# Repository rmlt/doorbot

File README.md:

# doorbot
Software for our DoorBot

The DoorBot is a device connected to our doorphone that opens the office doors as required.

This software runs on a Raspberry Pi connected to a circuit board that allows it to:
* get input from the doorphone LED and the doorbell button
* simulate pressing a button on the doorphone
* move a servo attached to the door handle
* play sounds

TODO:
* black, isort
* split into modules
* logging instead of printing
* add some photos

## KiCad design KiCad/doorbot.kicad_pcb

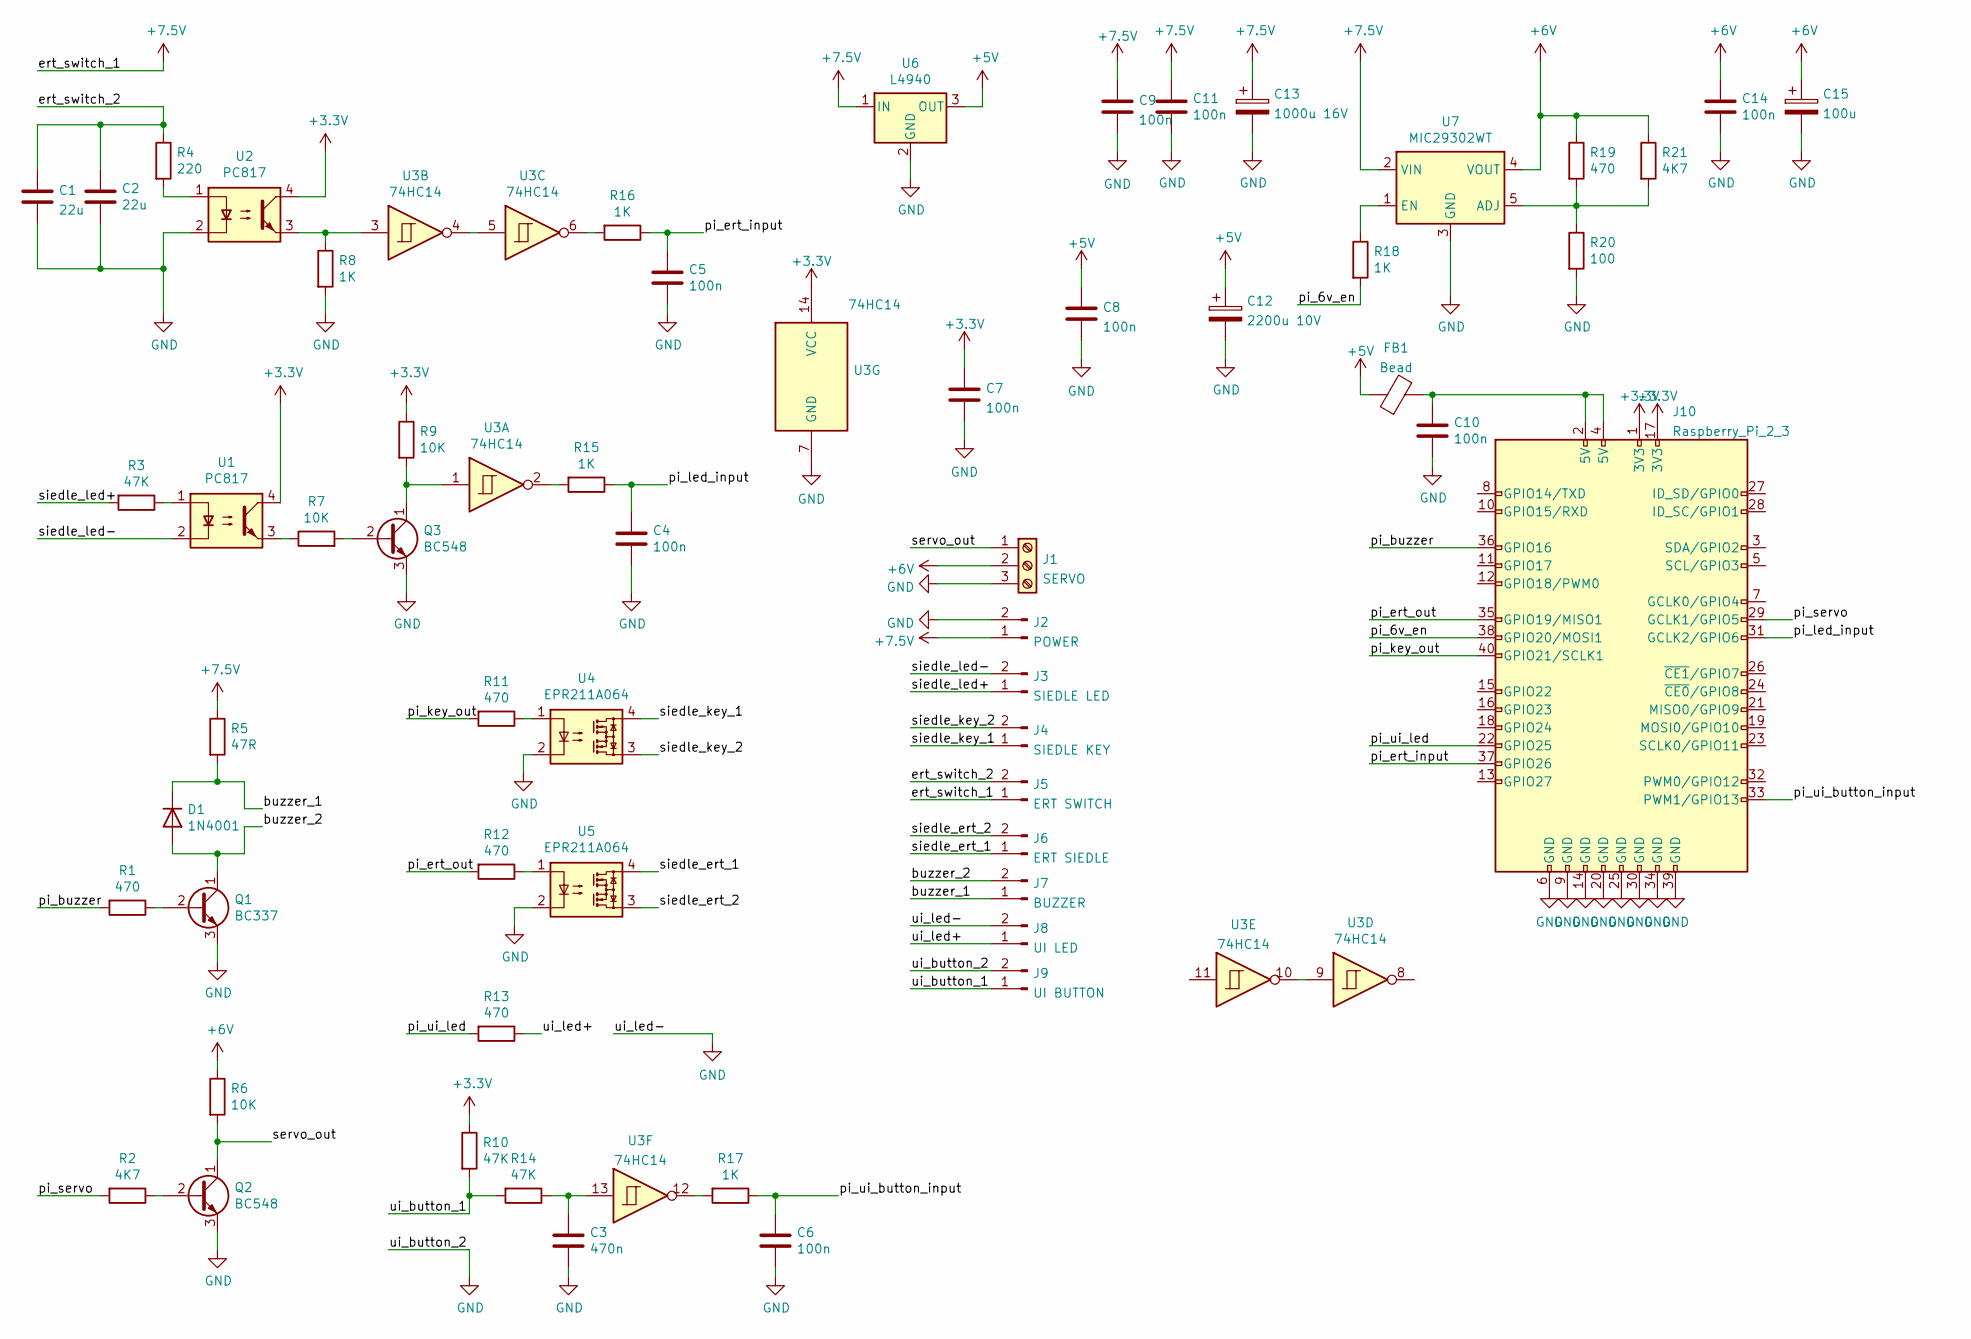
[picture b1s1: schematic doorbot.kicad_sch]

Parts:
C1, C2: 22u; C_1210_3225Metric
C3: 470n; C_Disc_D5.0mm_W2.5mm_P2.50mm
C4, C5, C6, C8, C9, C10, C11, C14: 100n; C_Disc_D5.0mm_W2.5mm_P2.50mm
C7: 100n; C_Disc_D7.5mm_W5.0mm_P7.50mm
C12: 2200u 10V; CP_Radial_D12.5mm_P5.00mm
C13: 1000u 16V; CP_Radial_D12.5mm_P5.00mm
C15: 100u; CP_Radial_D10.0mm_P2.50mm
D1: 1N4001; D_DO-41_SOD81_P2.54mm_Vertical_AnodeUp
FB1: Bead; R_Axial_DIN0207_L6.3mm_D2.5mm_P10.16mm_Horizontal
J1: SERVO; TerminalBlock_bornier-3_P5.08mm
J2: POWER; PinHeader_1x02_P2.54mm_Vertical
J3: SIEDLE LED; PinHeader_1x02_P2.54mm_Vertical
J4: SIEDLE KEY; PinHeader_1x02_P2.54mm_Vertical
J5: ERT SWITCH; PinHeader_1x02_P2.54mm_Vertical
J6: ERT SIEDLE; PinHeader_1x02_P2.54mm_Vertical
J7: BUZZER; PinHeader_1x02_P2.54mm_Vertical
J8: UI LED; PinHeader_1x02_P2.54mm_Vertical
J9: UI BUTTON; PinHeader_1x02_P2.54mm_Vertical
J10: Raspberry_Pi_2_3; PinSocket_2x20_P2.54mm_Vertical
Q1: BC337; TO-92_Inline_Wide
Q2, Q3: BC548; TO-92_Inline_Wide
R1, R19: 470; R_Axial_DIN0207_L6.3mm_D2.5mm_P2.54mm_Vertical
R2, R21: 4K7; R_Axial_DIN0207_L6.3mm_D2.5mm_P2.54mm_Vertical
R3, R14: 47K; R_Axial_DIN0207_L6.3mm_D2.5mm_P5.08mm_Vertical
R4: 220; R_Axial_DIN0207_L6.3mm_D2.5mm_P2.54mm_Vertical
R5: 47R; R_Axial_DIN0207_L6.3mm_D2.5mm_P5.08mm_Vertical
R6: 10K; R_Axial_DIN0207_L6.3mm_D2.5mm_P2.54mm_Vertical
R7, R9: 10K; R_Axial_DIN0207_L6.3mm_D2.5mm_P10.16mm_Horizontal
R8: 1K; R_Axial_DIN0207_L6.3mm_D2.5mm_P10.16mm_Horizontal
R10: 47K; R_Axial_DIN0309_L9.0mm_D3.2mm_P12.70mm_Horizontal
R11, R13: 470; R_Axial_DIN0207_L6.3mm_D2.5mm_P5.08mm_Vertical
R12: 470; R_Axial_DIN0207_L6.3mm_D2.5mm_P10.16mm_Horizontal
R15: 1K; R_Axial_DIN0309_L9.0mm_D3.2mm_P12.70mm_Horizontal
R16: 1K; R_Axial_DIN0207_L6.3mm_D2.5mm_P15.24mm_Horizontal
R17: 1K; R_Axial_DIN0207_L6.3mm_D2.5mm_P2.54mm_Vertical
R18: 1K; R_Axial_DIN0207_L6.3mm_D2.5mm_P5.08mm_Vertical
R20: 100; R_Axial_DIN0207_L6.3mm_D2.5mm_P5.08mm_Vertical
U1, U2: PC817; DIP-4_W7.62mm
U3: 74HC14; DIP-14_W7.62mm
U4, U5: EPR211A064; DIP-4_W7.62mm
U6: L4940; TO-220-3_Horizontal_TabDown
U7: MIC29302WT; R_Array_SIP5

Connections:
+3V3: C7.1, J10.1 (3V3), J10.17 (3V3), R9.1, R10.1, U1.4, U2.4, U3.14 (VCC)
+5V: C8.1, C12.1, FB1.1, U6.3 (OUT)
+6V: C14.1, C15.1, J1.2, R6.1, R19.1, R21.1, U7.4 (VOUT)
+7.5V: C9.1, C11.1, C13.1, J2.1, J5.1, R5.1, U6.1 (IN), U7.2 (VIN)
/buzzer_1: D1.1 (K), J7.1, R5.2
/buzzer_2: D1.2 (A), J7.2, Q1.1 (C)
/ert_switch_2: C1.1, C2.1, J5.2, R4.1
/pi_6v_en: J10.38 (GPIO20/MOSI1), R18.2
/pi_buzzer: J10.36 (GPIO16), R1.2
/pi_ert_input: C5.1, J10.37 (GPIO26), R16.1
/pi_ert_out: J10.35 (GPIO19/MISO1), R12.2
/pi_key_out: J10.40 (GPIO21/SCLK1), R11.2
/pi_led_input: C4.1, J10.31 (GCLK2/GPIO6), R15.1
/pi_servo: J10.29 (GCLK1/GPIO5), R2.2
/pi_ui_button_input: C6.1, J10.33 (PWM1/GPIO13), R17.1
/pi_ui_led: J10.22 (GPIO25), R13.2
/servo_out: J1.1, Q2.1 (C), R6.2
/siedle_ert_1: J6.1, U5.4
/siedle_ert_2: J6.2, U5.3
/siedle_key_1: J4.1, U4.4
/siedle_key_2: J4.2, U4.3
/siedle_led+: J3.1, R3.2
/siedle_led-: J3.2, U1.2
/ui_button_1: J9.1, R10.2, R14.2
/ui_led+: J8.1, R13.1
GND: C1.2, C2.2, C3.2, C4.2, C5.2, C6.2, C7.2, C8.2, C9.2, C10.2, C11.2, C12.2, C13.2, C14.2, C15.2, J1.3, J2.2, J8.2, J9.2, J10.6 (GND), J10.9 (GND), J10.14 (GND), J10.20 (GND), J10.25 (GND), J10.30 (GND), J10.34 (GND), J10.39 (GND), Q1.3 (E), Q2.3 (E), Q3.3 (E), R8.2, R20.2, U2.2, U3.7 (GND), U4.2, U5.2, U6.2 (GND), U7.3 (GND)
unnamed: C3.1, R14.1, U3.13
unnamed: C10.1, FB1.2, J10.2 (5V), J10.4 (5V)
unnamed: Q1.2 (B), R1.1
unnamed: Q2.2 (B), R2.1
unnamed: Q3.1 (C), R9.2, U3.1
unnamed: Q3.2 (B), R7.2
unnamed: R3.1, U1.1
unnamed: R4.2, U2.1
unnamed: R7.1, U1.3
unnamed: R8.1, U2.3, U3.3
unnamed: R11.1, U4.1
unnamed: R12.1, U5.1
unnamed: R15.2, U3.2
unnamed: R16.2, U3.6
unnamed: R17.2, U3.12
unnamed: R18.1, U7.1 (EN)
unnamed: R19.2, R20.1, R21.2, U7.5 (ADJ)
unnamed: U3.4, U3.5
unnamed: U3.9, U3.10

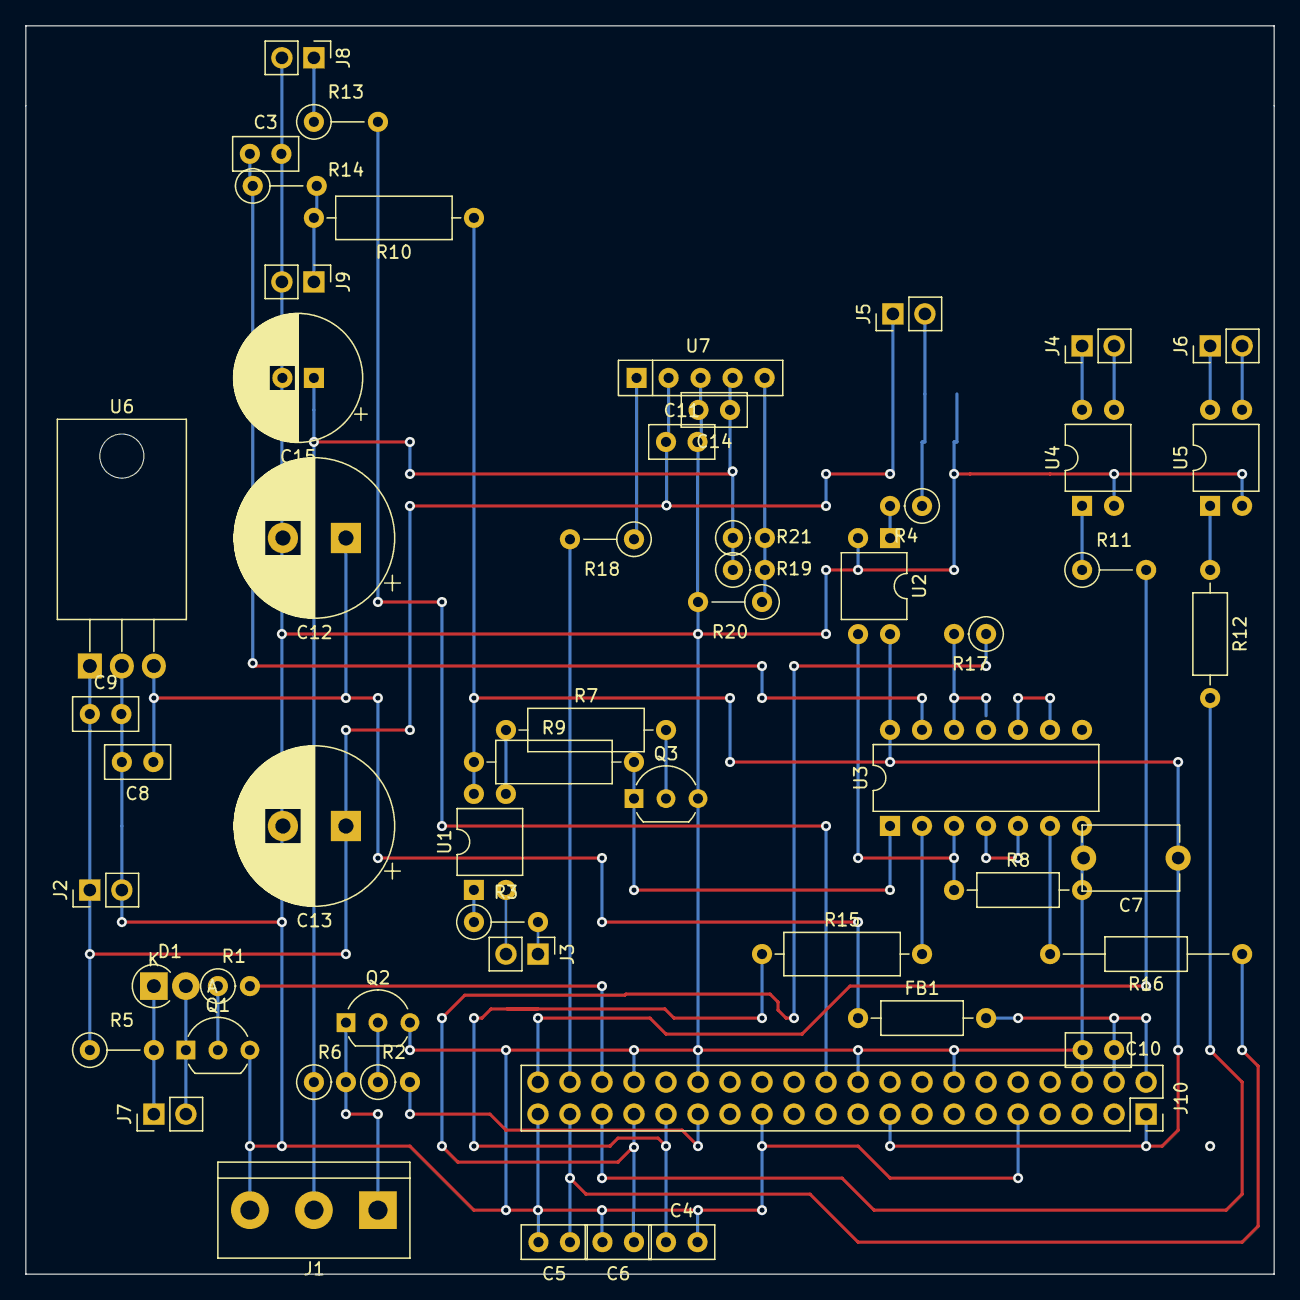
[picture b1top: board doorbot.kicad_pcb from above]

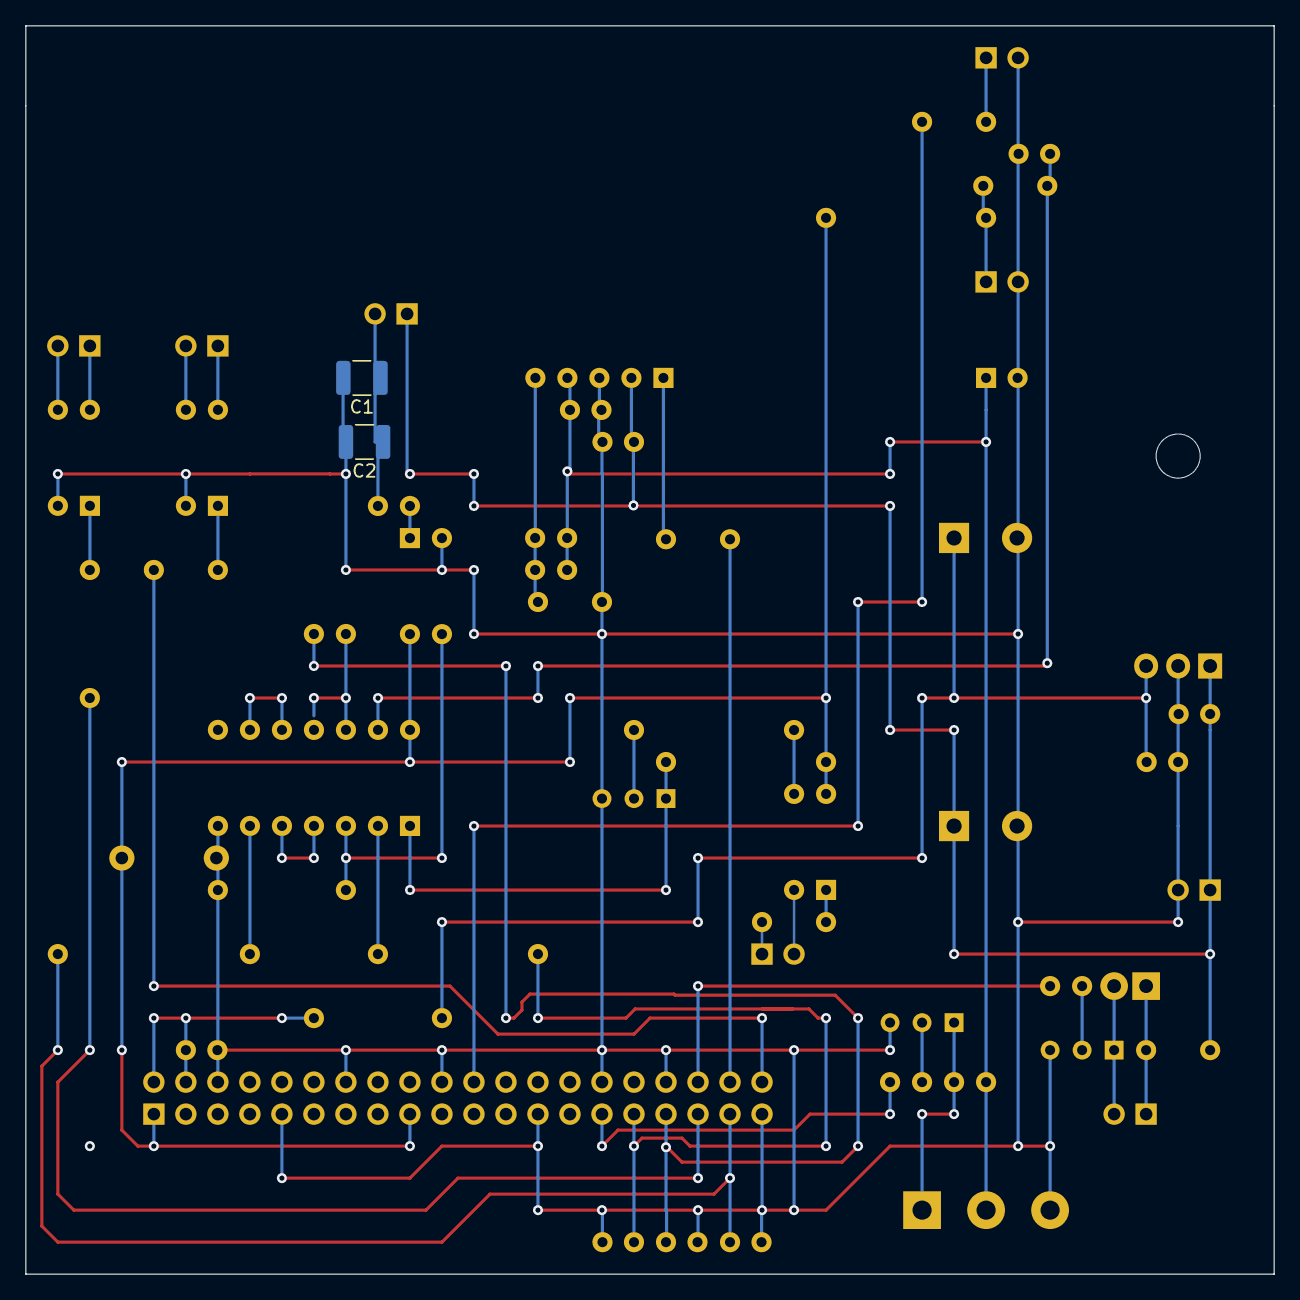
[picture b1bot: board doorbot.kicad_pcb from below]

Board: 2 copper layers, 99.1 x 99.1 mm, 58 parts (2 on the bottom side), 45 nets.

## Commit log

2020-08-06 Implement opening the remote door
2020-09-02 Rename GPIO pins
2020-09-02 Implement heartbeat blink
2020-09-02 Implement delayed access on the weekend; temporary until chatbot
2020-10-02 Implement opening the door when the button is pressed (for tests only)
2020-10-02 Implement doorbell button press detection for door opening
2020-10-02 Adjust access times after time zone change
2020-10-02 Add missing initial values for output GPIO pins
2020-10-05 Handle RISING event on INDICATOR_LED_INPUT_GPIO (hardware change)
2021-12-06 Move the most commonly edited settings to a separate file
2021-12-06 Add simple sound capability
2021-12-06 Play chirps for doorbell and key button press confirmation
2021-12-14 Add some basic information to the README
2022-01-24 Add circuit diagram
2022-02-14 Migrate schematic to KiCad 6, add connectors and Raspberry Pi
2022-02-14 Add netlist and initial PCB
2022-02-21 Route the stripboard PCB
2022-02-21 Add UI button GPIO assignment
2022-04-27 Add the final PCB version
2022-04-27 Tweak constants, add comments
2022-04-27 Add support for UI button
2022-04-27 Add a test chirp
2022-05-13 Add settings comments
2022-05-13 Implement the free-office-access mode
2022-05-16 Reorder imports
2022-05-19 Implement proper handling of single long presses
2022-05-19 Fix multiple-door-opening problem
